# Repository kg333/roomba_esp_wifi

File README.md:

# roomba_esp_wifi
Board for adding wifi using ESP-12 to Roomba 500/600 series.

## Overview

This project describes a board with an ESP-12 microcontroller and the following interfaces:
* UART - 3.3V, 5.0V tolerant
* Battery input - supports 4.75V - 36V
* GPIO - single pin at 3.3V
* 3.3V auxiliary output

It is intended for use with [esp-roomba-mqtt by John Boiles](https://github.com/johnboiles/esp-roomba-mqtt), but may also be suitable for general use in battery-powered applications.

## Layout

## Parts

| Quantity | Part Description       | Suggested Part Number |
| -------- | --------------------   | --------------------- |
|        1 | ESP-12E or ESP-12F     | N/A                   |
|        2 | Small push buttons     | PTS820J15MSMTRLFS     |
|        2 | Resistor, 470Ω, 0805   | ERJ-6ENF4700V         |
|        6 | Resistor, 12KΩ, 0805   | ERJ-6ENF1182V         |
|        1 | Resistor, 6.04KΩ, 0805 | ERJ-6ENF6041V         |
|        2 | Capacitor, 10µF, 0805  | C0805C106K3PAC7800    |
|        1 | 1x7 100mil header (optional)      | PPPC071LFBN-RC        |
|        1 | 3.3V DC-DC Converter     | TSR 1-2433     |

## Programming

This board can be intially programmed in a similar fashion to a NodeMCU using your preferred Arduino programmer, but does require manual control using the PRGM and RST buttons.  If using esp-roomba-mqtt, it may be programmed over Wifi after the initial flash.

## Installation

The board is designed to fit inside a Roomba 560 behind the starboard wheel well.  It is recommended to solder wires between the board and the rear of the Roomba Mini-DIN port to avoid having a Mini-DIN plug sticking up from the Roomba.

### Installation location on Roomba 560

### Board wired in

### Final installation

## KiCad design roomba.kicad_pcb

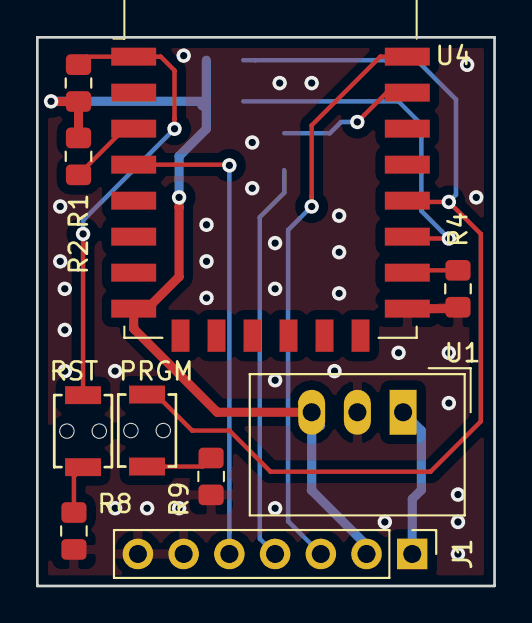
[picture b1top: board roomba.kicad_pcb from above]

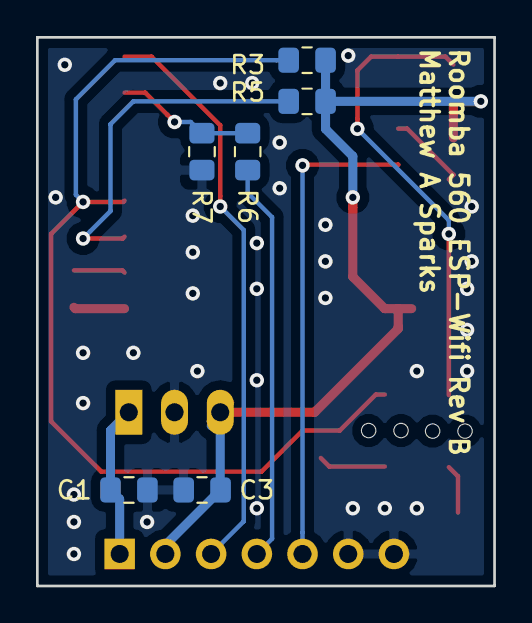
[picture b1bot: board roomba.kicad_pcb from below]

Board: 2 copper layers, 25.4 x 30.5 mm, 16 parts (6 on the bottom side), 14 nets.

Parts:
C1, C3: 10 uF; C_0805_2012Metric_Pad1.15x1.40mm_HandSolder
J1: Conn_01x07_Male; PinHeader_1x07_P2.54mm_Vertical
PRGM: SW_Push; PTS820
R1, R2, R3, R4, R5, R7: 12K; R_0805_2012Metric_Pad1.15x1.40mm_HandSolder
R6: 6.04K; R_0805_2012Metric_Pad1.15x1.40mm_HandSolder
R8, R9: 470; R_0805_2012Metric_Pad1.15x1.40mm_HandSolder
RST: SW_Push; PTS820
U1: TSR_1-2433; Converter_DCDC_TRACO_TSR-1_THT
U4: ESP-12F; ESP-12E

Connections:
+3V3: C3.1, J1.2, R1.2, R2.2, R3.2, R5.2, U1.3, U4.8
+BATT: C1.1, J1.1, U1.1
/GPIO0: PRGM.1, R3.1, U4.18
/GPIO2: R5.1, U4.17
/LOCAL_BRC: J1.5, U4.4
/LOCAL_RXD: R6.1, R7.2, U4.21
/LOCAL_TXD: J1.3, U4.22
/ROOMBA_TXD: J1.4, R6.2
Earth: C1.2, C3.2, J1.6, J1.7, R4.2, R7.1, R8.1, R9.1, U1.2, U4.15
unnamed: R1.1, RST.1, U4.1
unnamed: R2.1, U4.3
unnamed: R4.1, U4.16
unnamed: R8.2, RST.2
unnamed: PRGM.2, R9.2

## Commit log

2018-08-30 Initial prototype for Roomba wifi circuit
2018-09-09 Adding Roomba dev board schematic output
2018-10-05 Updating circuit for Roomba PCB part placement complete
    Adding ESP8266 part libraries
2018-10-05 Routed PCB for Roomba
2018-10-05 Adding silkscreen and title/date information.
2018-10-05 Updated layout to a 1 by 1.2 inch size. Components are now on both sides. Solder Mask Clearance adjusted to 0.002in
2018-10-22 Removed TXB0104, since it was garbling UART. Instead added voltage divider on TXD from Roomba, and ran RXD and BRC to Roomba directly.
2018-11-02 Updating Roomba project to use buttons for reset/programming. Removing 5V to 3.3V translator in favor of voltage divider. Removing 5V to 3.3V regulator and going directly from BATT to 3.3V.
2019-01-07 Updating documentation and adding licensing for this project and kicad-ESP8266 by jdunmire.
2019-01-07 Fixing license typos
2019-01-07 Adding installation images
2019-01-07 Adding README.md
2019-01-07 Deleting backup file
